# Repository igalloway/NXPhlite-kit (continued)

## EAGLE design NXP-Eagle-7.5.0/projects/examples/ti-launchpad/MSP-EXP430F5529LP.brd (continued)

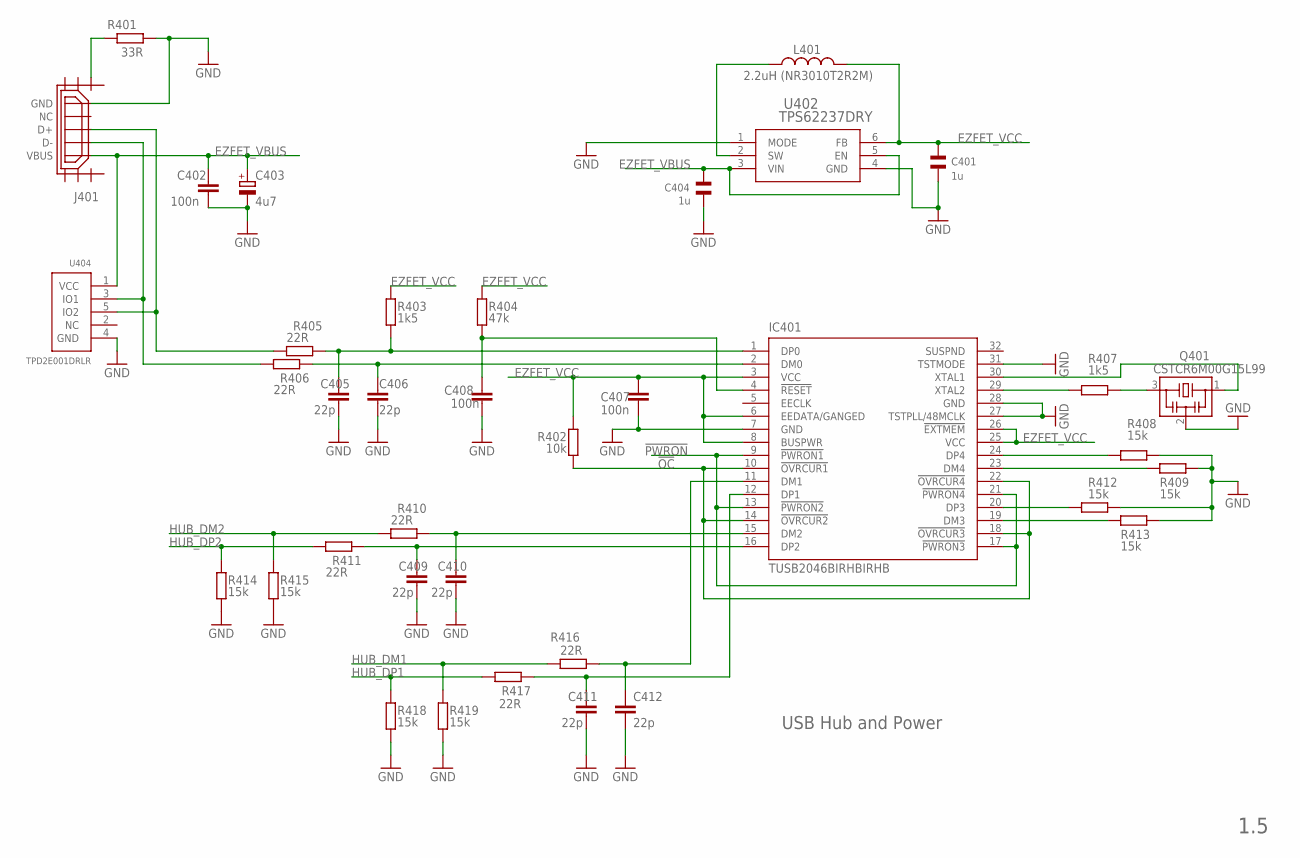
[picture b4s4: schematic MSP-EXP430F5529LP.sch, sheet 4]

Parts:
C401, C404: 1u; CSMD0805
C402, C407, C408: 100n; C0402
C403: 4u7; A/3216-18R
C405, C406, C409, C410, C411, C412: 22p; C0402
IC401: TUSB2046BIRHBIRHB; RHB_S-PQFP-N32
J401: USB_MICRO_FLIPPED; HIROSE-ZX62R-B-5P
L401: 2.2uH (NR3010T2R2M); L-NR3010
Q401: CSTCR6M00G15L99; MURATA-FILTER_CSTCR
R401: 33R; R0402
R402: 10k; R0402
R403, R407: 1k5; R0402
R404: 47k; R0402
R405, R406, R410, R411, R416, R417: 22R; R0402
R408, R409, R412, R413, R414, R415, R418, R419: 15k; R0402
U402: TPS62237DRY; DRY6
U404: TPD2E001DRLR; TPD2E001-DRL

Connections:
!OC: IC401.10 (!OVRCUR1), IC401.14 (!OVRCUR2), IC401.18 (!OVRCUR3), IC401.22 (!OVRCUR4), R402.2
!PWRON: IC401.9 (!PWRON1), IC401.13 (!PWRON2), IC401.17 (!PWRON3), IC401.21 (!PWRON4)
EZFET_VBUS: C402.1, C403.+, C404.2, J401.VBUS, U402.3 (VIN), U402.5 (EN), U404.1 (VCC); also elsewhere on the board
EZFET_VCC: C401.2, C407.1, IC401.3 (VCC), IC401.6 (EEDATA/GANGED), IC401.8 (BUSPWR), IC401.25 (VCC), IC401.26 (!EXTMEM), L401.P$2 (2), R402.1, R403.1, R404.1, U402.6 (FB); also elsewhere on the board
GND: C401.1, C402.2, C403.-, C404.1, C405.2, C406.2, C407.2, C408.2, C409.2, C410.2, C411.2, C412.2, IC401.7 (GND), IC401.27 (TSTPLL/48MCLK), IC401.28 (GND), IC401.31 (TSTMODE), J401.GND, Q401.2, R401.2, R408.1, R409.1, R412.1, R413.1, R414.2, R415.2, R418.2, R419.2, U402.1 (MODE), U402.4 (GND), U404.4 (GND); also elsewhere on the board
HUB_DM1: R416.2, R419.1; also elsewhere on the board
HUB_DM2: R410.2, R415.1; also elsewhere on the board
HUB_DP1: R417.2, R418.1; also elsewhere on the board
HUB_DP2: R411.2, R414.1; also elsewhere on the board
unnamed: C410.1, IC401.15 (DM2), R410.1
unnamed: C405.1, IC401.1 (DP0), R403.2, R405.1
unnamed: IC401.30 (XTAL1), Q401.1
unnamed: J401.SHIELD1, R401.1
unnamed: C406.1, IC401.2 (DM0), R406.1
unnamed: J401.D+, R405.2, U404.5 (IO2)
unnamed: J401.D-, R406.2, U404.3 (IO1)
unnamed: L401.P$1 (1), U402.2 (SW)
unnamed: IC401.29 (XTAL2), R407.2
unnamed: C412.1, IC401.11 (DM1), R416.1
unnamed: C411.1, IC401.12 (DP1), R417.1
unnamed: C409.1, IC401.16 (DP2), R411.1
unnamed: C408.1, IC401.4 (!RESET), R404.2
unnamed: IC401.20 (DP3), R412.2
unnamed: IC401.24 (DP4), R408.2
unnamed: IC401.23 (DM4), R409.2
unnamed: IC401.19 (DM3), R413.2
unnamed: Q401.3, R407.1

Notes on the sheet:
USB Hub and Power
1.5

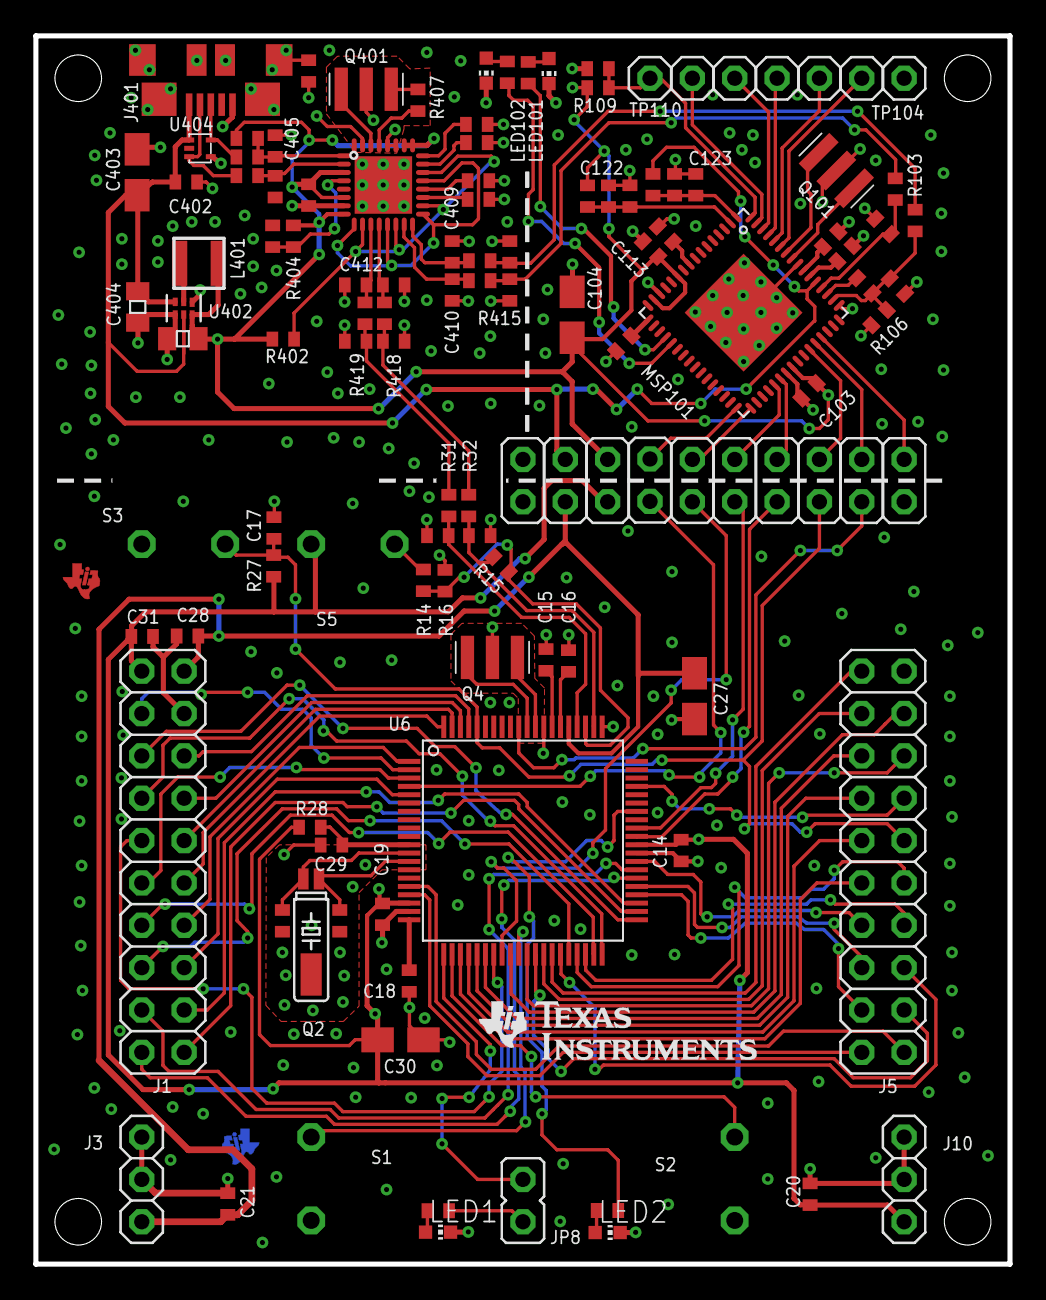
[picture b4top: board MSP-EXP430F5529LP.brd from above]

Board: 2 copper layers, 58.4 x 73.7 mm, 132 parts (1 on the bottom side), 117 nets.

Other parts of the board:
DRAW2: LOGO-ROCKET-10X7MM-BRD
U$1: LOGO16_TPLACE
U$2, U$5: TILOGO_SMALL

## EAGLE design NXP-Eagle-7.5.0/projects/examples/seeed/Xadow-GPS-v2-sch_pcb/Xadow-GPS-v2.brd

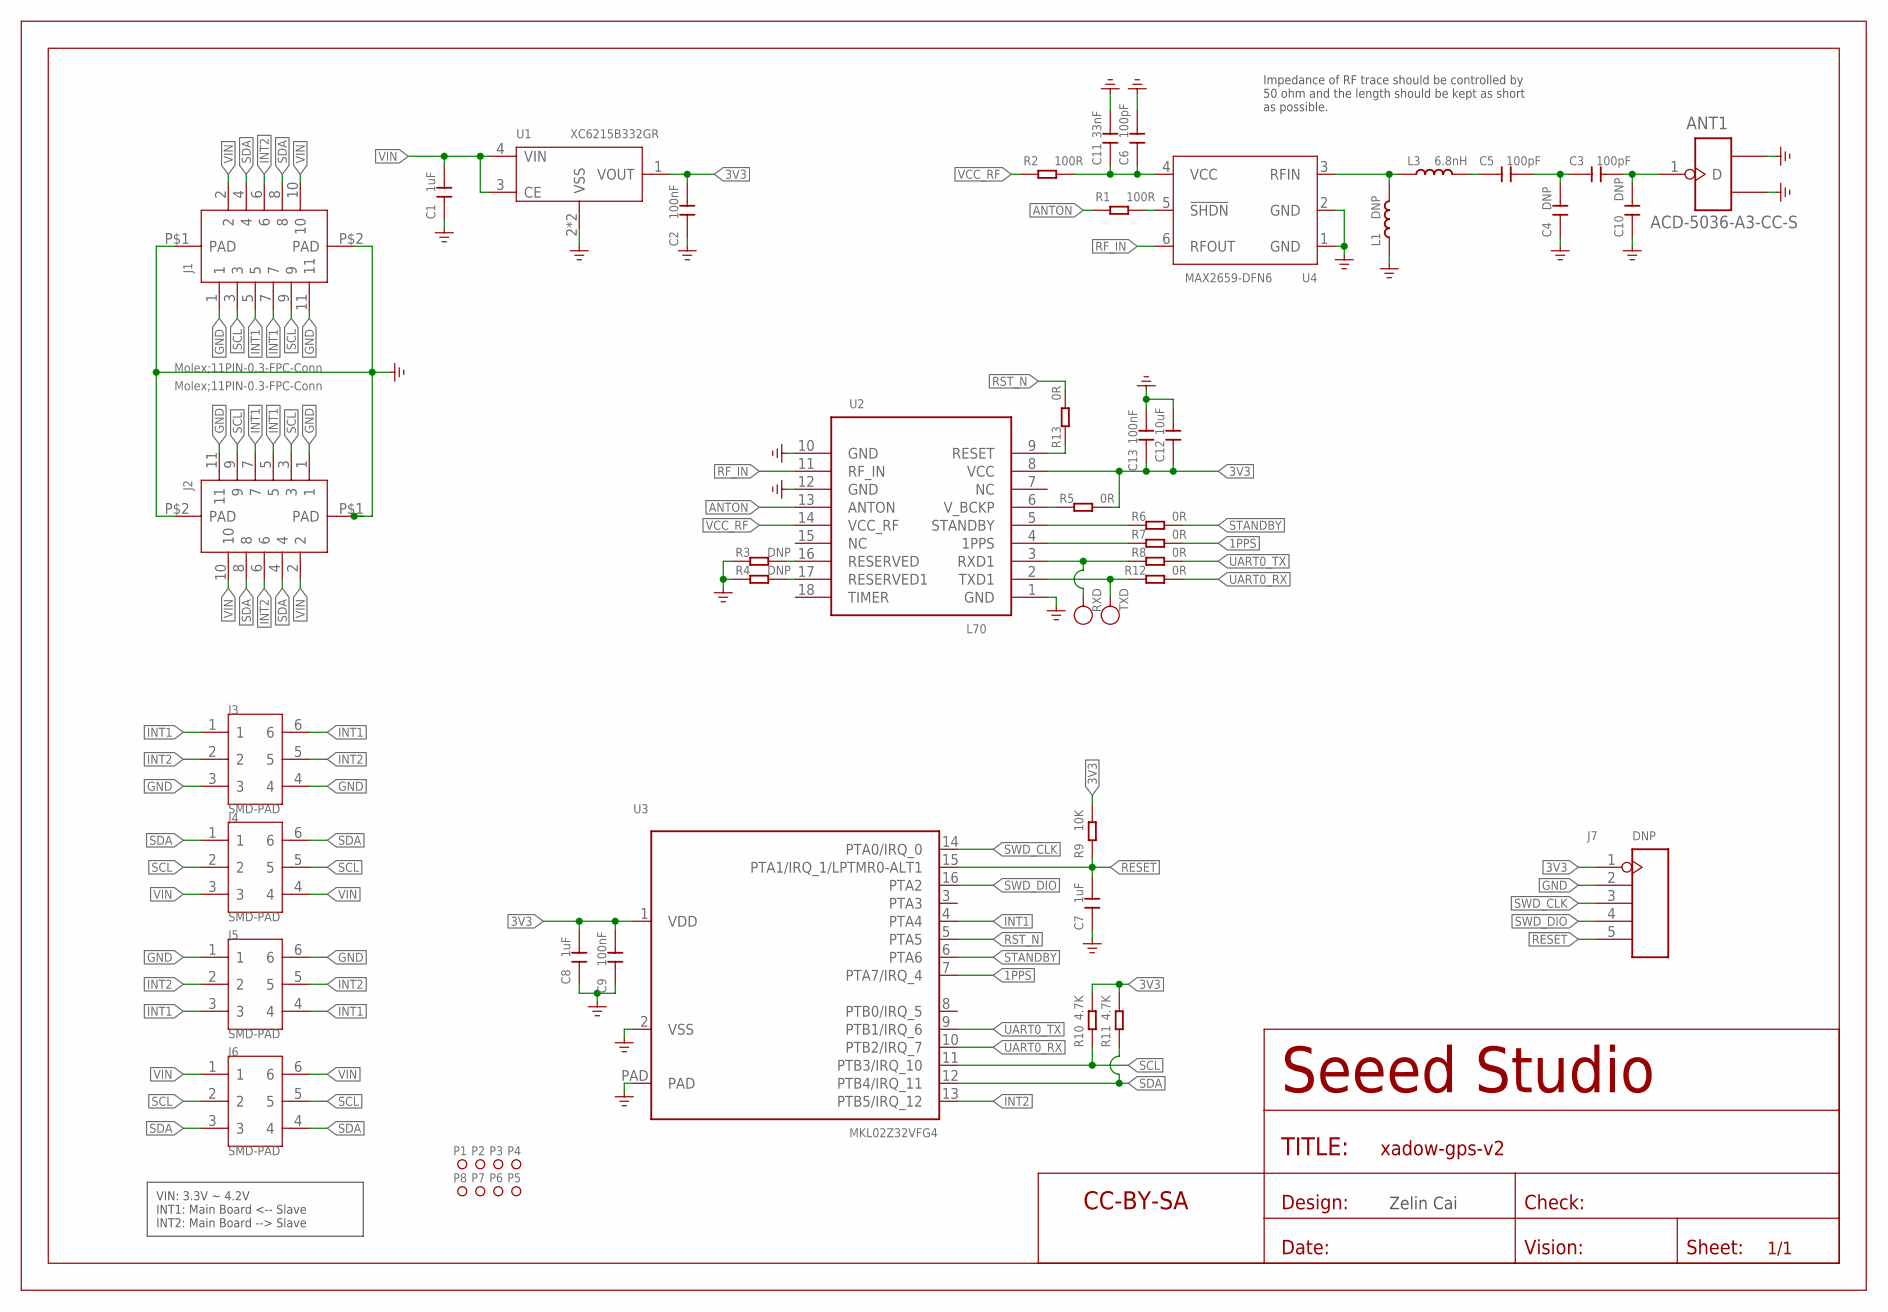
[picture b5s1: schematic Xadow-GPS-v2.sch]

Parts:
ANT1: ACD-5036-A3-CC-S; ANT3-SMD-5.2X3.7X0.7MM
C1, C8: 1uF; C0402
C2, C9, C13: 100nF; C0201
C3, C5, C6: 100pF; C0201
C4, C10: DNP; C0201
C7: 1uF; C0201
C11: 33nF; C0201
C12: 10uF; C0402
FR: PAGE1; SEEEDSTUDIO-PCB-FRAME
J1, J2: Molex;11PIN-0.3-FPC-Conn; FPC11-SMD-0.3(FH35C)
J3, J5: SMD-PAD; 6P-DIP-2_ROUND
J4: SMD-PAD; 6P-DIP-2
J6: SMD-PAD; 6P-DIP-2_S3
J7: DNP; H5-SMD-2.0-TEST
L1: DNP; L0201
L3: 6.8nH; L0201
P1, P2, P3, P4, P5, P6, P7, P8: MRK; ROUND-MARK-1.0
R1, R2: 100R; R0201
R3, R4: DNP; R0201
R5, R6, R7, R8, R12, R13: 0R; R0201
R9: 10K; R0201
R10, R11: 4.7K; R0201
RXD: RXD; TP-D45MIL
TXD: TXD; TP-D45MIL
U1: XC6215B332GR; USP4-0.6-1.2X1.6MM
U2: L70; LGA18-1.1-9.7X10.1X2.5MM
U3: MKL02Z32VFG4; QFN16G-0.5-3X3MM
U4: MAX2659-DFN6; DFN6-0.5-1.5X1.2X0.72MM

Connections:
1PPS: R7.1, U3.7 (PTA7/IRQ_4)
3V3: C2.2, C8.2, C9.2, C12.1, C13.1, J7.1, R5.1, R9.2, R10.2, R11.2, U1.1 (VOUT), U2.8 (VCC), U3.1 (VDD)
!RESET: C7.2, J7.5, R9.1, U3.15 (PTA1/IRQ_1/LPTMR0-ALT1)
ANTON: R1.2, U2.13 (ANTON)
GND: ANT1.2 (GND1), ANT1.3 (GND2), C1.1, C2.1, C4.1, C6.2, C7.1, C8.1, C9.1, C10.1, C11.2, C12.2, C13.2, J1.1, J1.11, J1.P$1 (PAD), J1.P$2 (PAD), J2.1, J2.11, J2.P$1 (PAD), J2.P$2 (PAD), J3.3, J3.4, J5.1, J5.6, J7.2, L1.1, R3.2, R4.2, U1.2 (VSS), U1.PAD (VSS), U2.1 (GND), U2.10 (GND), U2.12 (GND), U3.2 (VSS), U3.PAD, U4.1 (GND), U4.2 (GND)
INT1: J1.5, J1.7, J2.5, J2.7, J3.1, J3.6, J5.3, J5.4, U3.4 (PTA4)
INT2: J1.6, J2.6, J3.2, J3.5, J5.2, J5.5, U3.13 (PTB5/IRQ_12)
unnamed: C3.1, C4.2, C5.2
unnamed: ANT1.1 (D), C3.2, C10.2
unnamed: L1.2, L3.1, U4.3 (RFIN)
unnamed: C5.1, L3.2
unnamed: R1.1, U4.5 (!SHDN)
unnamed: C6.1, C11.1, R2.1, U4.4 (VCC)
unnamed: R3.1, U2.16 (RESERVED)
unnamed: R4.1, U2.17 (RESERVED1)
unnamed: R5.2, U2.6 (V_BCKP)
unnamed: R6.2, U2.5 (STANDBY)
unnamed: R7.2, U2.4 (1PPS)
unnamed: R13.2, U2.9 (RESET)
RF_IN: U2.11 (RF_IN), U4.6 (RFOUT)
RST_N: R13.1, U3.5 (PTA5)
RXD1: R8.2, RXD.T, U2.3 (RXD1)
SCL: J1.3, J1.9, J2.3, J2.9, J4.2, J4.5, J6.2, J6.5, R10.1, U3.11 (PTB3/IRQ_10)
SDA: J1.4, J1.8, J2.4, J2.8, J4.1, J4.6, J6.3, J6.4, R11.1, U3.12 (PTB4/IRQ_11)
STANDBY: R6.1, U3.6 (PTA6)
SWD_CLK: J7.3, U3.14 (PTA0/IRQ_0)
SWD_DIO: J7.4, U3.16 (PTA2)
TXD1: R12.2, TXD.T, U2.2 (TXD1)
UART0_RX: R12.1, U3.10 (PTB2/IRQ_7)
UART0_TX: R8.1, U3.9 (PTB1/IRQ_6)
VCC_RF: R2.2, U2.14 (VCC_RF)
VIN: C1.2, J1.2, J1.10, J2.2, J2.10, J4.3, J4.4, J6.1, J6.6, U1.3 (CE), U1.4 (VIN)

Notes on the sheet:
Zelin Cai
Impedance of RF trace should be controlled by 50 ohm and the length should be kept as short as possible.
VIN: 3.3V ~ 4.2V INT1: Main Board <-- Slave INT2: Main Board --> Slave

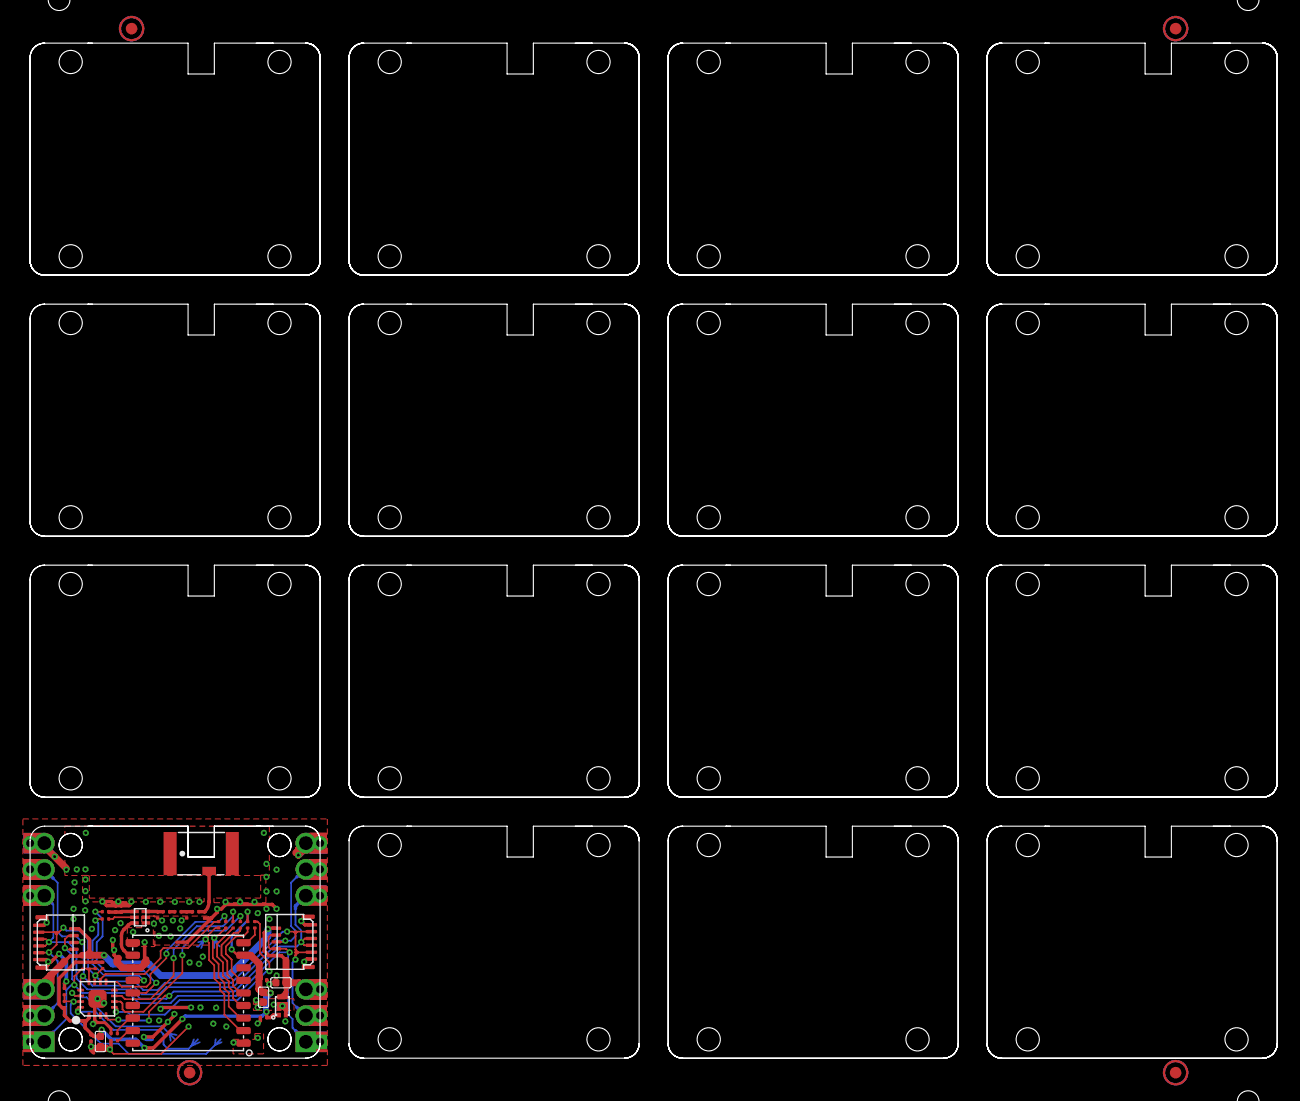
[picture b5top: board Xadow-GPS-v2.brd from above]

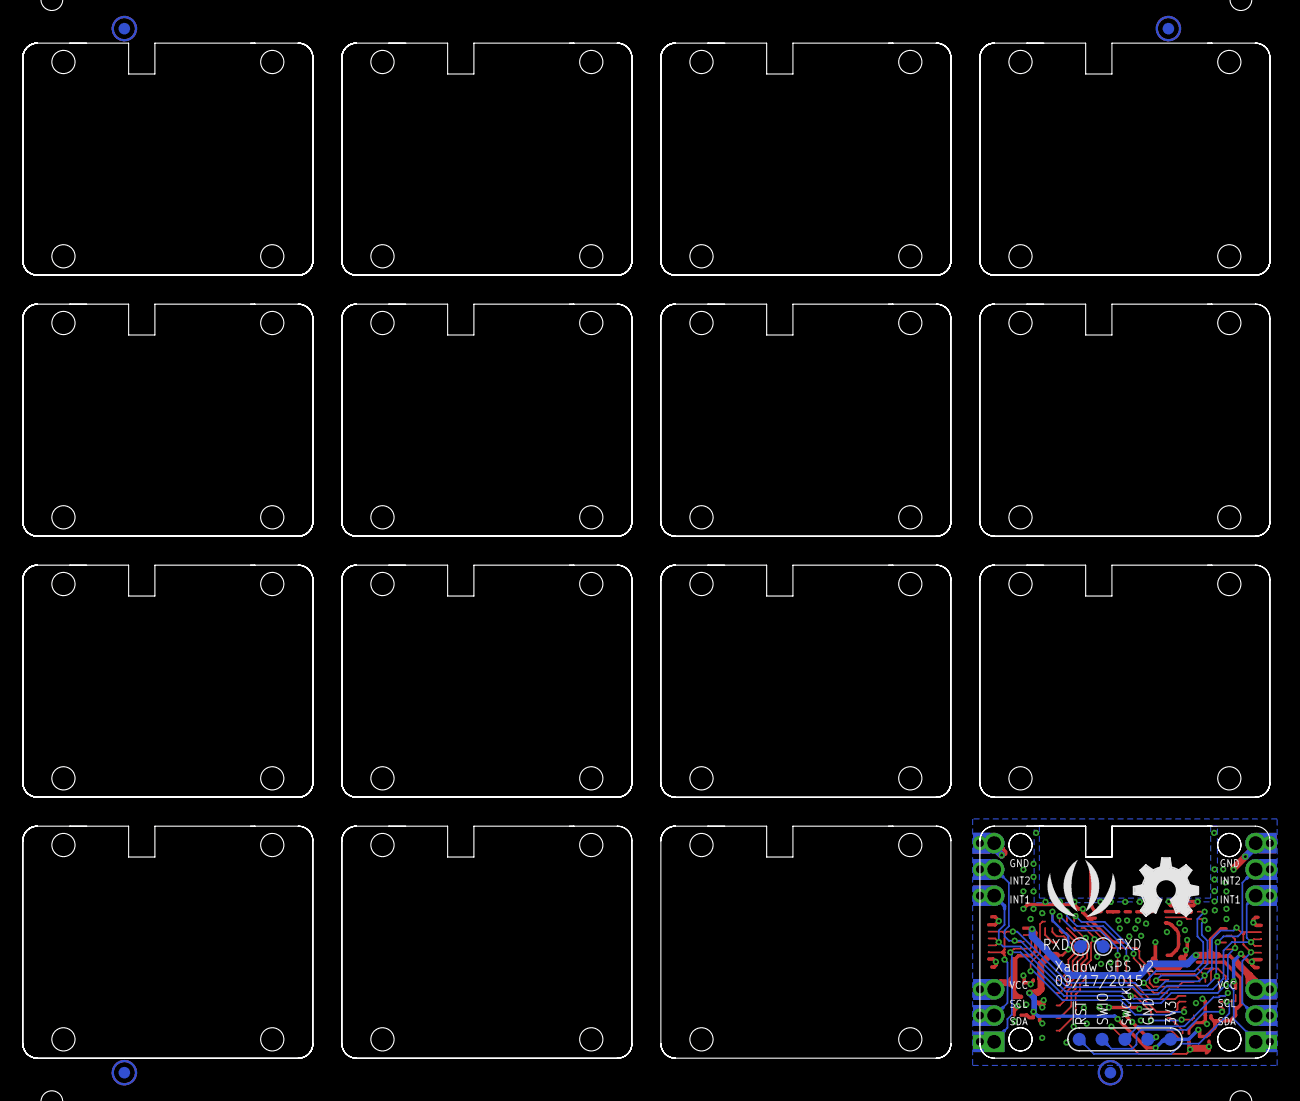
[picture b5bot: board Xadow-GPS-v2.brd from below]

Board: 2 copper layers, 109.2 x 88.9 mm, 53 parts (9 on the bottom side), 32 nets.

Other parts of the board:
U$19: OSHW_FILLX200_NOTEXT
U$21: SEEED-SILK-280*268MIL

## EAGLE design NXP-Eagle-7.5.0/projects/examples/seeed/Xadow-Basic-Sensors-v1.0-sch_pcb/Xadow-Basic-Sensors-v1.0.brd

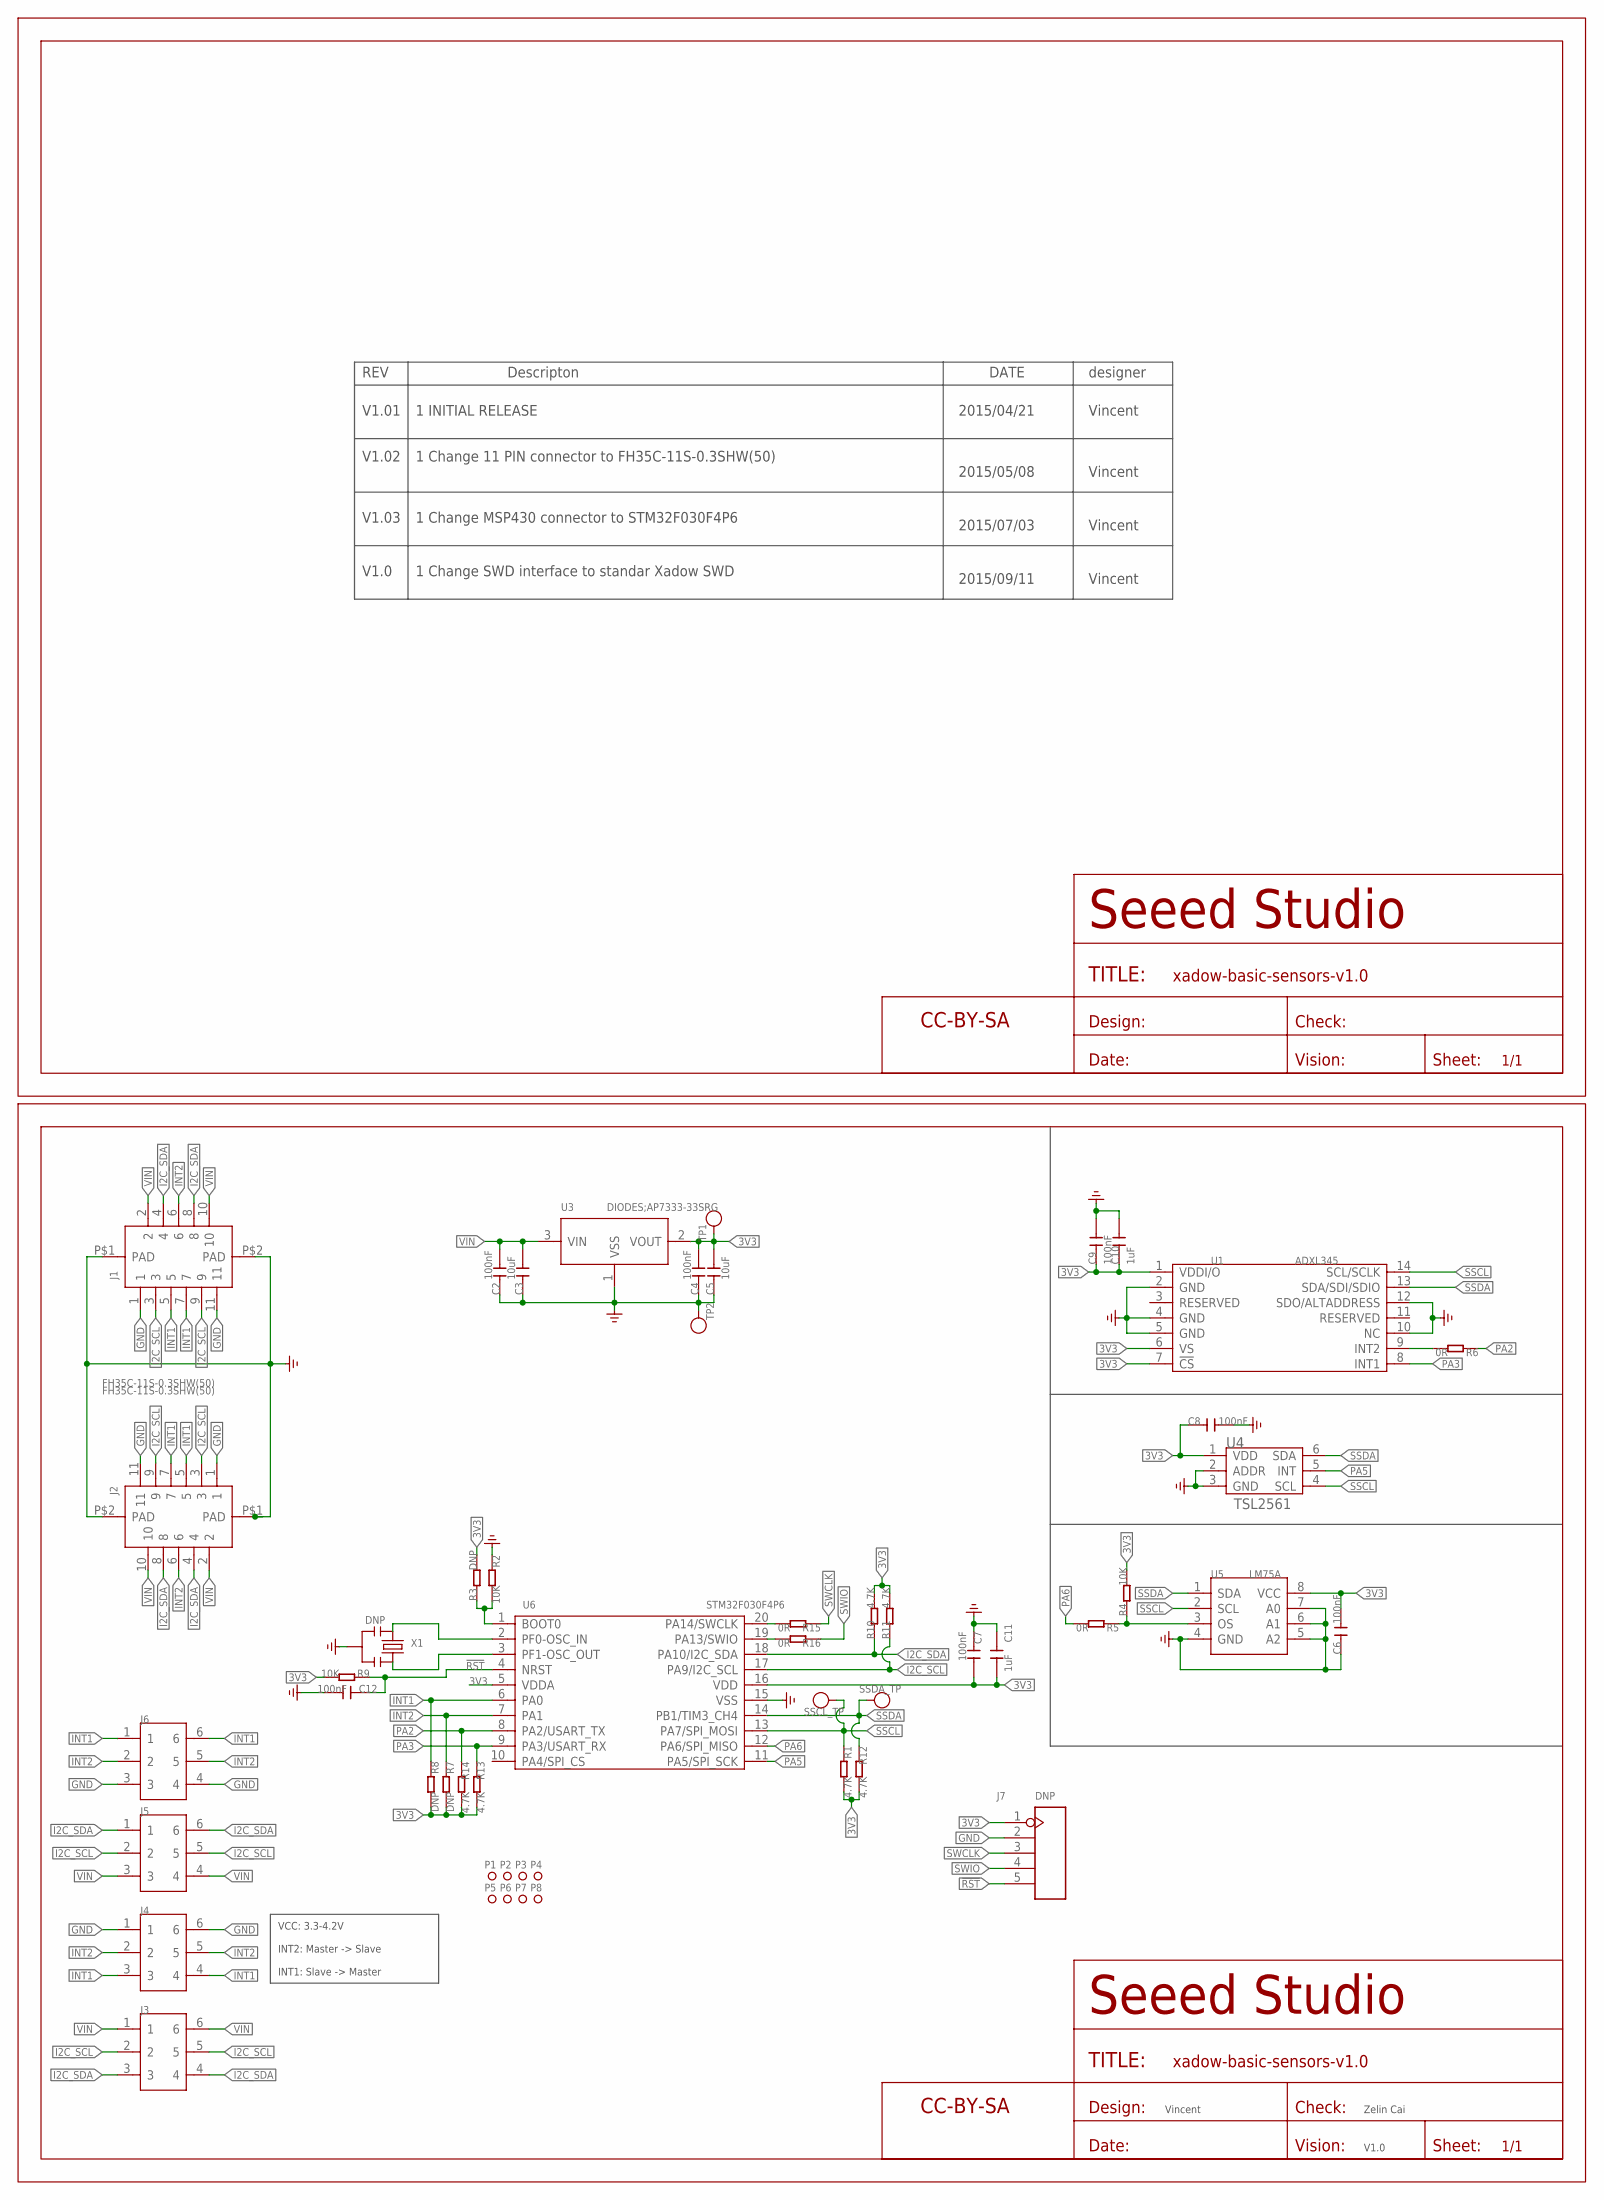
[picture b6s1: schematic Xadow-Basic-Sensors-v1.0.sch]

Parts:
C2, C4, C6, C7, C8, C9, C12: 100nF; C0402
C3, C5: 10uF; C0603
C10, C11: 1uF; C0402
FR1: SEEEDSTUDIO-OPEN-SCH-FRAME; SEEEDSTUDIO-PCB-FRAME
J1, J2: FH35C-11S-0.3SHW(50); FPC11-SMD-0.3(FH35C)
J3: HEADER6_S3; 6P-DIP-2_S3
J4, J6: HEADER6_ROUND; 6P-DIP-2_ROUND
J5: HEADER6; 6P-DIP-2
J7: DNP; H5-SMD-2.0-TEST
P1, P2, P3, P4, P5, P6, P7, P8: MARK-1.0'ANNULAR'; ROUND-MARK-1.0
R1, R10, R11, R12, R13, R14: 4.7K; R0402
R2, R4, R9: 10K; R0402
R3, R7, R8: DNP; R0402
R5, R6, R15, R16: 0R; R0402
SSCL_TP: TEST-POINT'4545'; TP-D45MIL
SSDA_TP: TEST-POINT'4545'; TP-D45MIL
TP1, TP2: TEST-POINT'4545'; TP-D45MIL
U1: ADXL345; LGA14
U3: DIODES;AP7333-33SRG; SOT-23
U4: TSL2561; TMB-6
U5: LM75A; TSSOP8-0.65-3X3MM
U6: STM32F030F4P6; TSSOP20-0.65-6.5X4.4MM
U$2: SEEEDSTUDIO-OPEN-SCH-FRAME; SEEEDSTUDIO-PCB-FRAME
X1: DNP; RESONATOR3-SMD-3.6X1.3X0.8MM

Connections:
3V3: C4.2, C5.2, C6.2, C7.2, C8.1, C9.1, C10.1, C11.2, J7.1, R1.2, R3.2, R4.2, R7.2, R8.2, R9.2, R10.2, R11.2, R12.2, R13.2, R14.2, TP1.T, U1.1 (VDDI/O), U1.6 (VS), U1.7 (!CS), U3.2 (VOUT), U4.1 (VDD), U5.8 (VCC), U6.5 (VDDA), U6.16 (VDD)
!RST: C12.1, J7.5, R9.1, U6.4 (NRST)
GND: C2.1, C3.1, C4.1, C5.1, C6.1, C7.1, C8.2, C9.2, C10.2, C11.1, C12.2, J1.1, J1.11, J1.P$1 (PAD), J1.P$2 (PAD), J2.1, J2.11, J2.P$1 (PAD), J2.P$2 (PAD), J4.1, J4.6, J6.3, J6.4, J7.2, R2.1, TP2.T, U1.2 (GND), U1.4 (GND), U1.5 (GND), U1.10 (NC), U1.12 (SDO/ALTADDRESS), U3.1 (VSS), U4.2 (ADDR), U4.3 (GND), U5.4 (GND), U5.5 (A2), U5.6 (A1), U5.7 (A0), U6.15 (VSS), X1.2
I2C_SCL: J1.3, J1.9, J2.3, J2.9, J3.2, J3.5, J5.2, J5.5, R11.1, U6.17 (PA9/I2C_SCL)
I2C_SDA: J1.4, J1.8, J2.4, J2.8, J3.3, J3.4, J5.1, J5.6, R10.1, U6.18 (PA10/I2C_SDA)
INT1: J1.5, J1.7, J2.5, J2.7, J4.3, J4.4, J6.1, J6.6, R8.1, U6.6 (PA0)
INT2: J1.6, J2.6, J4.2, J4.5, J6.2, J6.5, R7.1, U6.7 (PA1)
unnamed: R6.2, U1.9 (INT2)
unnamed: U6.2 (PF0-OSC_IN), X1.3
unnamed: R4.1, R5.1, U5.3 (OS)
unnamed: U6.3 (PF1-OSC_OUT), X1.1
unnamed: R2.2, R3.1, U6.1 (BOOT0)
unnamed: R15.2, U6.20 (PA14/SWCLK)
unnamed: R16.2, U6.19 (PA13/SWIO)
PA2: R6.1, R14.1, U6.8 (PA2/USART_TX)
PA3: R13.1, U1.8 (INT1), U6.9 (PA3/USART_RX)
PA5: U4.5 (INT), U6.11 (PA5/SPI_SCK)
PA6: R5.2, U6.12 (PA6/SPI_MISO)
SSCL: R1.1, SSCL_TP.T, U1.14 (SCL/SCLK), U4.4 (SCL), U5.2 (SCL), U6.13 (PA7/SPI_MOSI)
SSDA: R12.1, SSDA_TP.T, U1.13 (SDA/SDI/SDIO), U4.6 (SDA), U5.1 (SDA), U6.14 (PB1/TIM3_CH4)
SWCLK: J7.3, R15.1
SWIO: J7.4, R16.1
VIN: C2.2, C3.2, J1.2, J1.10, J2.2, J2.10, J3.1, J3.6, J5.3, J5.4, U3.3 (VIN)

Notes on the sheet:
Vincent
Zelin Cai
V1.0
INT1: Slave -> Master
INT2: Master -> Slave
VCC: 3.3-4.2V
REV
Descripton
DATE
designer
V1.01
1 INITIAL RELEASE
V1.02
1 Change 11 PIN connector to FH35C-11S-0.3SHW(50)
2015/04/21
2015/05/08
V1.03
2015/07/03
1 Change MSP430 connector to STM32F030F4P6
2015/09/11
1 Change SWD interface to standar Xadow SWD

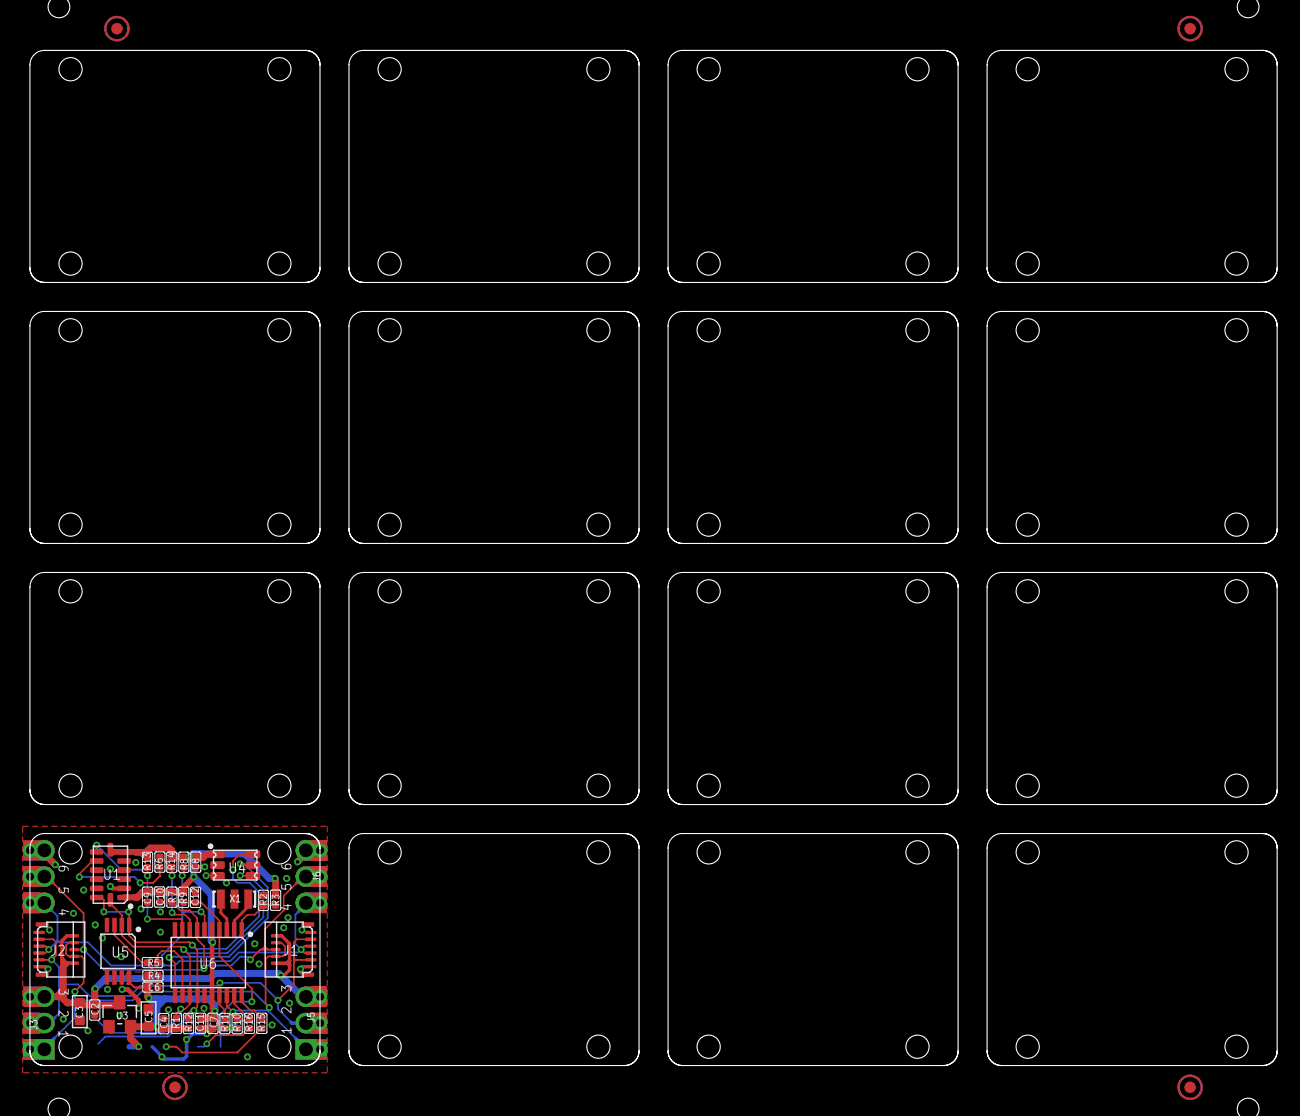
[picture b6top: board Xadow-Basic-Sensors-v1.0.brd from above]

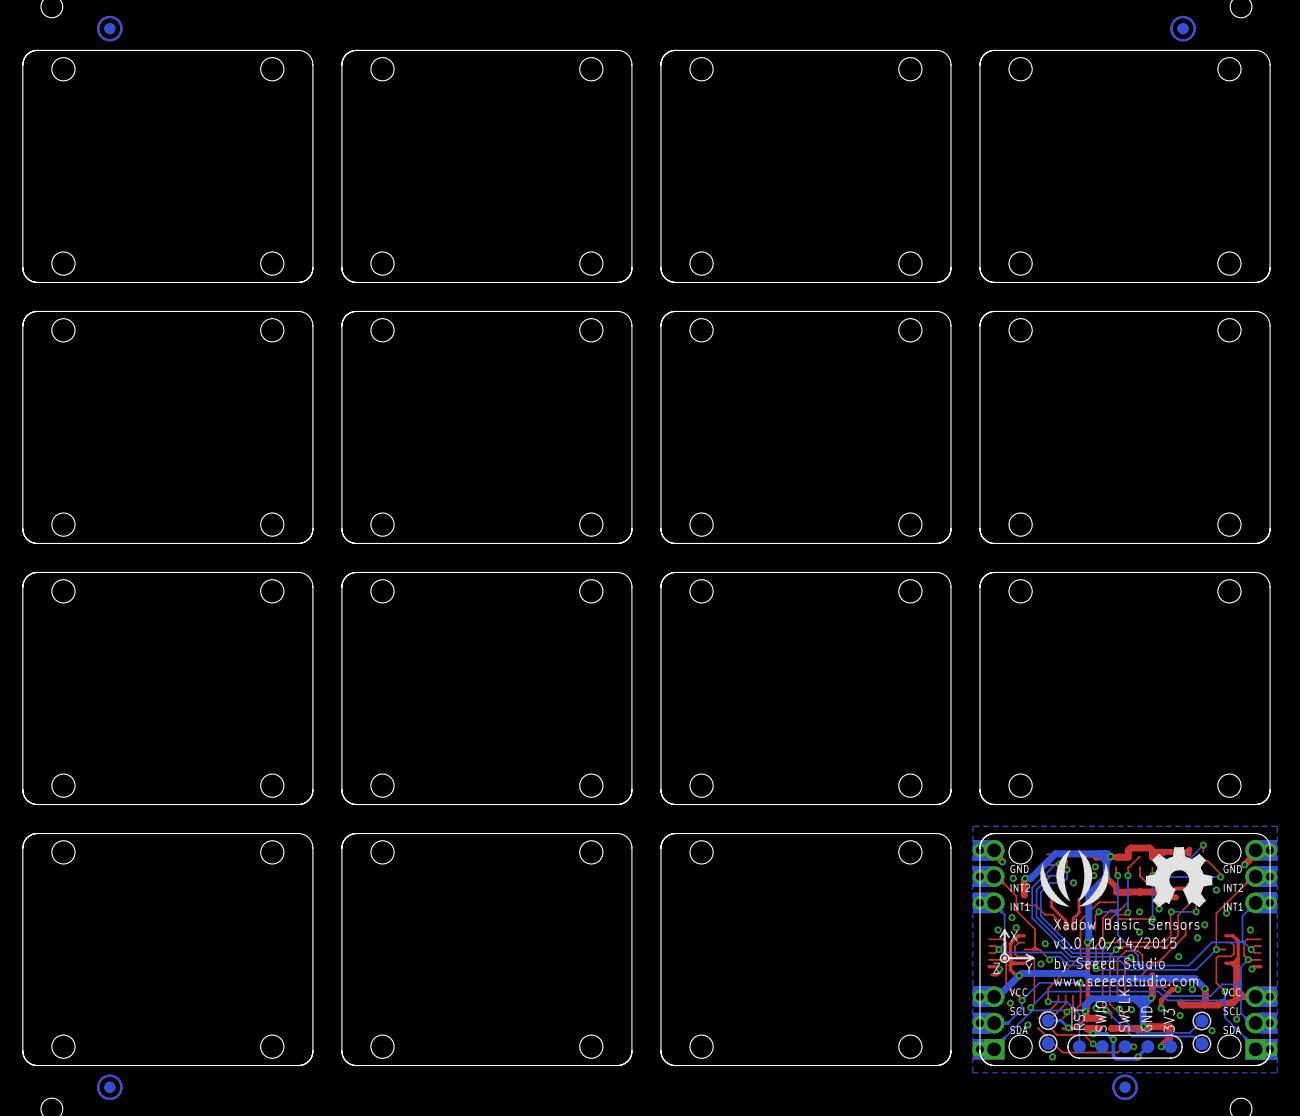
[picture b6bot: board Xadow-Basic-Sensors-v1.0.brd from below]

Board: 2 copper layers, 109.2 x 88.9 mm, 56 parts (11 on the bottom side), 23 nets.

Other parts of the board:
U$18: OSHW_FILLX200_NOTEXT
U$20: SEEED-SILK-280*268MIL
